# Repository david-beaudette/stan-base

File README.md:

### Install RPi Pico SDK
In a personal folder called projects (could be other):
```bash
cd ~/projects
mkdir pico
cd pico
git clone -b master https://github.com/raspberrypi/pico-sdk.git
cd pico-sdk
git submodule update --init
cd ..
git clone -b master https://github.com/raspberrypi/pico-examples.git
sudo apt update
sudo apt install cmake gcc-arm-none-eabi libnewlib-arm-none-eabi build-essential
cd pico-examples
mkdir build
cd build
echo "export PICO_SDK_PATH=~/projects/pico-sdk" >> ~/.bashrc
source ~/.bashrc
cmake -DCMAKE_BUILD_TYPE=Debug ..
make -j4

```
### Install OpenOCD and debugger
```bash
cd ~/projects/pico
sudo apt install automake autoconf build-essential texinfo libtool libftdi-dev libusb-1.0-0-dev
git clone https://github.com/raspberrypi/openocd.git --recursive --branch rp2040 --depth=1
cd openocd
./bootstrap
./configure --enable-ftdi --enable-sysfsgpio --enable-bcm2835gpio
make -j4
sudo make install
sudo apt install gdb-multiarch

```
### OpenOCD Setup
Add username to the plugdev group to allow non-sudo access to any USB device:
```bash
echo 'SUBSYSTEM=="usb", MODE="0660", GROUP="plugdev"' | sudo tee /etc/udev/rules.d/00-usb-permissions.rules
udevadm control --reload-rules
sudo usermod -a -G plugdev [username]
```
Log out and back in.

### Debugging session
To debug, start opencd in a seperate terminal in the ~/projects/pico/openocd folder:
```bash
cd ~/projects/pico/openocd
src/openocd -f interface/picoprobe.cfg -f target/rp2040.cfg -s tcl
```

### Current state
## Battery voltage reading
Battery / motor ground is decoupled from digital ground. That is good, however the voltage reading is offset and unreliable because of this. Apparently with proper star grounding the grounds could be connected together without issues. Otherwise the most reliable way of achieving this would be to use a seperate DC/DC converter and ADC on the high-power side, and opto-coupler on the digital link to RP2040. 

## Orientation sensor calibration
A proper procedure to calibrate the BNO055 should be written. Ideally it should be automated when/if the robot can achieve it by itself.

## Serial communication with head
The link between base and head (ROS-based) was not completed yet.

## Stability
Finish test_ctl

## LCD
LCD is not working anymore...

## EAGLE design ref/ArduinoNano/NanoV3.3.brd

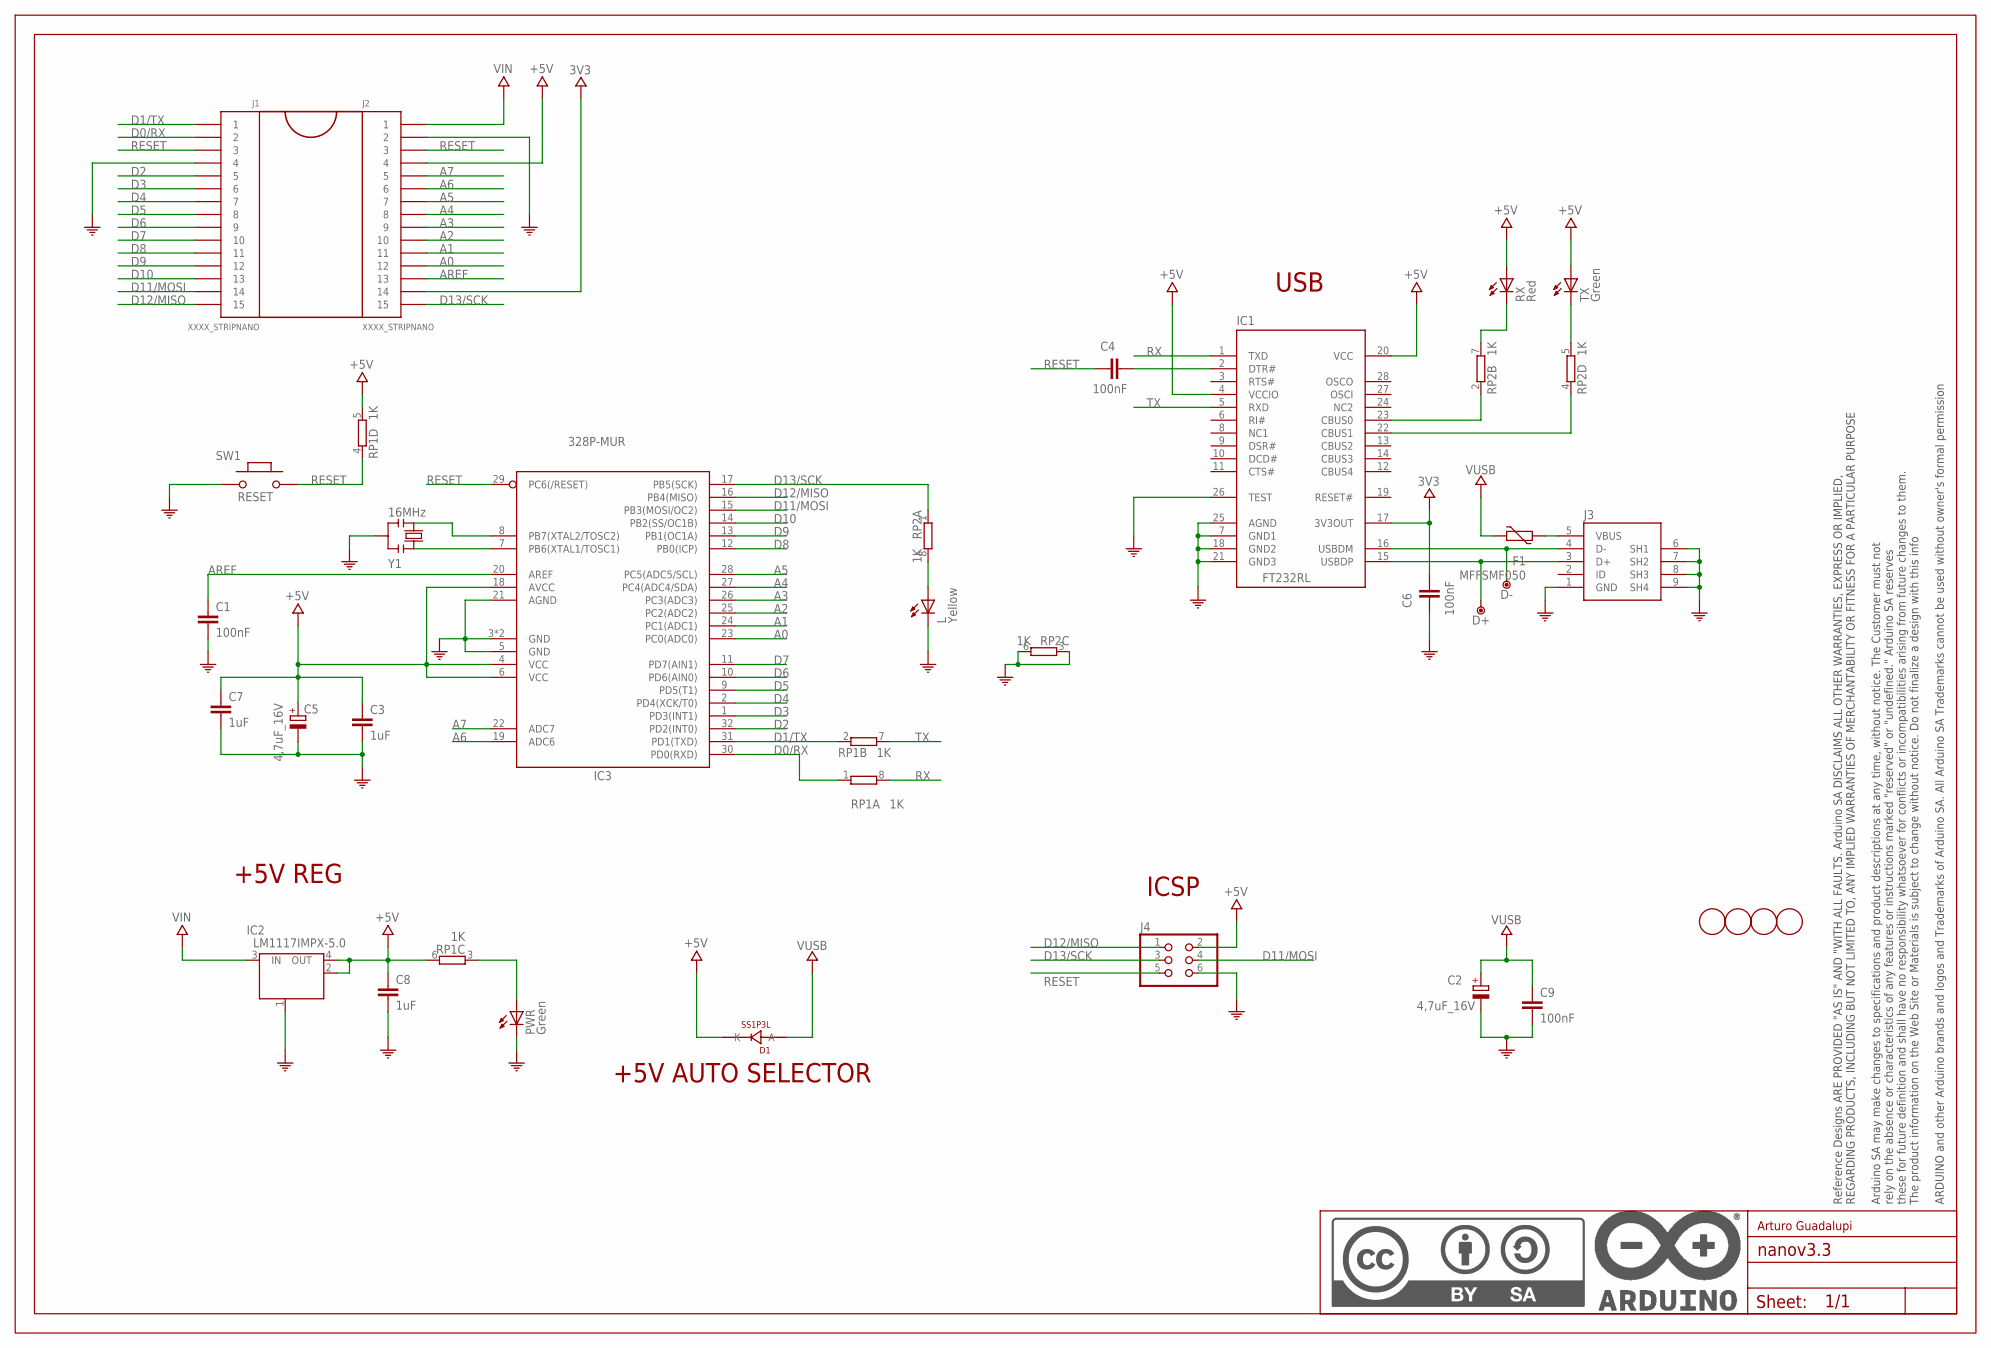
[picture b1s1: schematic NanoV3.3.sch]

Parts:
C1, C4, C6, C9: 100nF; C0603-ROUND
C2, C5: 4,7uF_16V; TAN-A
C3, C7, C8: 1uF; C0603-ROUND
D1: SS1P3L; DO220AAL
D+: DNP; TP-1.00MM
D-: DNP; TP-1.00MM
F1: MFFSMF050; 0603-1608X90N
FRAME1: DNP; FRAME
IC1: FT232RL; SSOP28
IC2: LM1117IMPX-5.0; LINEAR_SOT223
IC3: 328P-MUR; VQFN32
J1, J2: XXXX_STRIPNANO; HEAD15-NOSS
J3: 0219_14850; USB-MINI-B_2
J4: 0114_PH254-203DF118A00V; 2X03
L: Yellow; CHIPLED_0805
PWR: Green; CHIPLED_0805
RP1, RP2: 1K; CAY16
RX: Red; CHIPLED_0805
SW1: RESET; SMD_157SW
TX: Green; CHIPLED_0805
U$4, U$5, U$53, U$54: DNP; FD-1-1.5
Y1: 16MHz; RESONATOR

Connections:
3V3: C6.2, IC1.17 (3V3OUT), J2.14
+5V: C3.1, C5.1 (+), C7.1, C8.1, D1.P$1 (K), IC1.4 (VCCIO), IC1.20 (VCC), IC2.2 (OUT), IC2.4 (OUT), IC3.4 (VCC), IC3.6 (VCC), IC3.18 (AVCC), J2.4, J4.2, RP1.5 (2), RP1.6 (2), RX.A, TX.A
A0: IC3.23 (PC0(ADC0)), J2.12
A1: IC3.24 (PC1(ADC1)), J2.11
A2: IC3.25 (PC2(ADC2)), J2.10
A3: IC3.26 (PC3(ADC3)), J2.9
A4: IC3.27 (PC4(ADC4/SDA)), J2.8
A5: IC3.28 (PC5(ADC5/SCL)), J2.7
A6: IC3.19 (ADC6), J2.6
A7: IC3.22 (ADC7), J2.5
AREF: C1.1, IC3.20 (AREF), J2.13
COM: C1.2, C2.2 (-), C3.2, C5.2 (-), C6.1, C7.2, C8.2, C9.2, IC1.7 (GND1), IC1.18 (GND2), IC1.21 (GND3), IC1.25 (AGND), IC1.26 (TEST), IC2.1 (GND/ADJ), IC3.3 (GND), IC3.5 (GND), IC3.21 (AGND), IC3.33 (GND), J1.4, J2.2, J3.1 (GND), J3.6 (SH1), J3.7 (SH2), J3.8 (SH3), J3.9 (SH4), J4.6, L.C, PWR.C, RP2.3 (1), RP2.6 (2), SW1.1, Y1.2
D0/RX: IC3.30 (PD0(RXD)), J1.2, RP1.1
D1/TX: IC3.31 (PD1(TXD)), J1.1, RP1.2 (1)
D2: IC3.32 (PD2(INT0)), J1.5
D3: IC3.1 (PD3(INT1)), J1.6
D4: IC3.2 (PD4(XCK/T0)), J1.7
D5: IC3.9 (PD5(T1)), J1.8
D6: IC3.10 (PD6(AIN0)), J1.9
D7: IC3.11 (PD7(AIN1)), J1.10
D8: IC3.12 (PB0(ICP)), J1.11
D9: IC3.13 (PB1(OC1A)), J1.12
D10: IC3.14 (PB2(SS/OC1B)), J1.13
D11/MOSI: IC3.15 (PB3(MOSI/OC2)), J1.14, J4.4
D12/MISO: IC3.16 (PB4(MISO)), J1.15, J4.1
D13/SCK: IC3.17 (PB5(SCK)), J2.15, J4.3, RP2.1
unnamed: IC3.8 (PB7(XTAL2/TOSC2)), Y1.3
unnamed: IC3.7 (PB6(XTAL1/TOSC1)), Y1.1
unnamed: PWR.A, RP1.3 (1)
unnamed: C4.2, IC1.2 (DTR#)
unnamed: D+.X, IC1.15 (USBDP), J3.3 (D+)
unnamed: D-.X, IC1.16 (USBDM), J3.4 (D-)
unnamed: L.A, RP2.8 (2)
unnamed: IC1.23 (CBUS0), RP2.2 (1)
unnamed: IC1.22 (CBUS1), RP2.4 (1)
unnamed: RP2.5 (2), TX.C
unnamed: F1.2, J3.5 (VBUS)
unnamed: RP2.7 (2), RX.C
RESET: C4.1, IC3.29 (PC6(/RESET)), J1.3, J2.3, J4.5, RP1.4 (1), SW1.2
RX: IC1.1 (TXD), RP1.8 (2)
TX: IC1.5 (RXD), RP1.7 (2)
VIN: IC2.3 (IN), J2.1
VUSB: C2.1 (+), C9.1, D1.P$2 (A), F1.1

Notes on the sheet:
+5V REG
ICSP
USB
+5V AUTO SELECTOR
Arturo Guadalupi

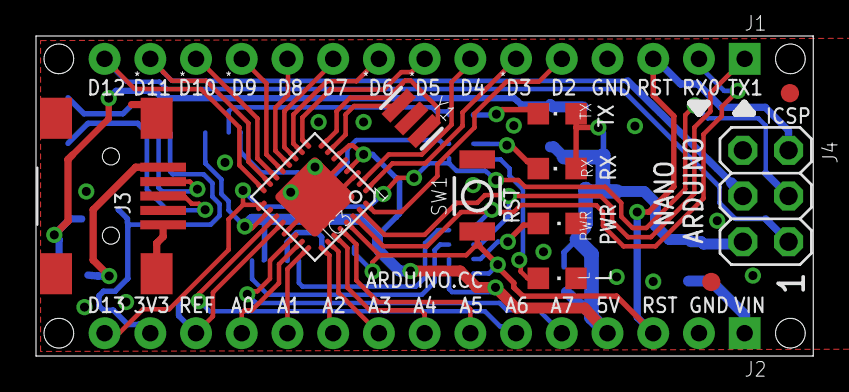
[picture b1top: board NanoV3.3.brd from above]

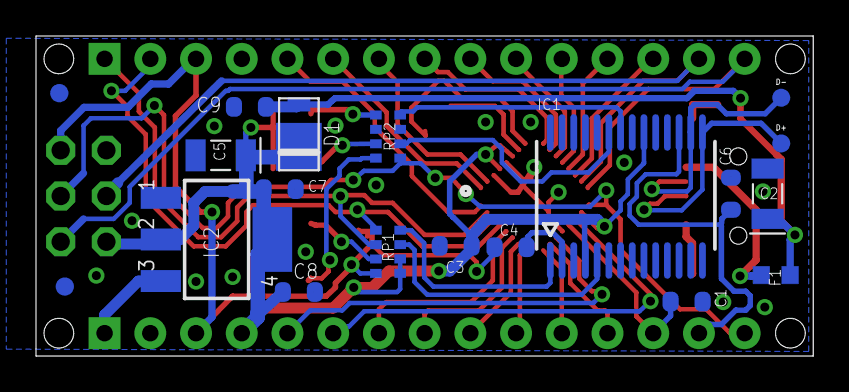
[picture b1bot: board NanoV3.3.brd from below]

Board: 2 copper layers, 43.2 x 17.8 mm, 33 parts (17 on the bottom side), 43 nets.

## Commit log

2021-03-05 Project creation.
2021-03-06 First code with motor driver.
2021-03-07 Interfaced with accelerometer and gyroscope.
2021-03-07 Started listing pins in hal.
2021-03-07 Setup ISR for accelerometer data.
2021-03-08 Added complementary filter and initial sensor bias / offset estimation.
2021-03-08 Starting moving from all in main( ) to periodic tasks.
2021-03-11 Modified code to use scheduled tasks.
2021-03-11 Integrated control function. Morors do not run smooth.
2021-03-12 Motors now orient with pitch. Integrated stepper library.
2021-03-20 Create CTL execute function to run in the main loop
2021-03-21 Added unit test to determine the motor top speed.
2021-03-28 Modified controller to use timer 1 without library.
2021-03-28 Fixed a few bugs. Still holes in the signal.
2021-03-29 Tried more ways to obtain better timing.
2021-03-29 Redesigned pulse generator with tick counter instead of overflow counter.
2021-03-30 Not much progress...
2021-03-31 Set local variables as volatile (not tested yet).
2021-04-01 Succeeded in generating the left motor pulse train.
2021-04-02 Generalised pulse generation for both motors. Still not working.
2021-04-03 Motor control test passed.
2021-04-03 Finalised test to produce expected results.
2021-04-03 Actual commit for last one.
2021-04-03 Modified to perform velocity control using pitch.
2021-04-04 Fixed accelerometer interrupt generation setting. Added state of charge computation to battery monitor function.
2021-04-04 Integrated PID library. Only compensating in one direction...
2021-04-05 Added test for serial communication.
2021-04-17 Linked stan-base with stan-common.
2021-04-18 Implemented serial protocol to send telemetry.
2021-04-18 Removed all serial prints except slow and fast packets.
2021-04-23 Implemented reception of commands.
2021-04-24 Optimised and protected complementary filter.
2021-04-25 Fixed gyro conversion from analog to deg/s.
2021-04-25 Added CRC to protocol. Reset pitch on filter init.
2021-05-01 Now initialisation of filter only averages gyro noise.
2021-05-02 Added tuning actions.
2021-05-08 Added command interface for motor enabling.
2021-05-15 Added tunable filter gain.
2021-05-16 Added system check task.
2021-05-16 Improved gyro bias estimation by using float.
2021-05-22 Prepared for PCB design
2021-05-23 Added more components for PCB design
2021-05-23 Added project specific libraries
2021-05-30 Relocated references and created Fritzing diagram.
2021-05-31 Finished first version of interconnexion diagram.
2021-06-04 Added interconnexion diagram version with connectors and another with protoboard.
2021-07-02 Set Arduino port for Linux
2021-07-02 Merged
2021-07-02 VSCode file was generated.
2021-07-31 Updated protoboard design.
2021-07-31 Started integrating camera module.
2021-07-31 Drafted servo driver based on timer 2 with 2 channels. Test fails.
2021-08-01 Finished implementing camera pan tilt control.
2021-08-01 Integrated cam pan tilt in main program.
2021-08-01 Eliminated some of the jitter when changing servo command.
2021-08-01 Implemented auto camera leveling.
2021-08-08 Setup for remote compilation from RPi.
2021-08-13 Added Python path required after syncing VSCode settings.
2021-10-07 Updated protoboard drawing.
2021-10-23 Added Pico reference
2021-11-06 Transferring code to RPi Pico. Dummy project was setup.
2021-11-07 Integrating rp2040 source in project.
2021-11-07 Added RP2040 reference files and Fritzing designs.
2021-11-07 Added hardware details.
2021-11-07 Created connection diagram for pico.
2021-11-13 Setup test build for camera control.
2021-11-13 Created files for unit test of camera control
2021-11-14 Finished implementing camera servo test.
2021-11-14 Created test and module for potentiometer.
2021-11-15 Used horner function for potentiometer measurement.
2021-11-15 Added potentiometer mapping function.
2021-11-15 Linked pot to camera pan.
2021-11-21 Integrated BNO055 library code and unit test.
2021-11-28 Corrected axis. Added missing state reads.
2021-11-28 Implemented battery voltage / SoC reading. Added motor control.
2021-12-18 Finalised draft of speed to PWM counter conversion function.
2022-01-01 Completed PWM controller. Microstepping control remains.
2022-01-02 Finalised auto control of period for fast / slow speed. Added a second motor test using pot.
2022-01-02 Added pulse counter on PWM.
2022-01-07 Added PID and NAV functions.
2022-01-09 Added reset function. Renamed enum members.
2022-01-09 Added controller function that uses both the motor and pid functions.
2022-01-09 Finished drafting control function.
2022-03-20 Added LCD documentation.
2022-03-20 Created breadboard interconnexion diagram with LCD.
2022-03-20 Added controller unit test (not implemented yet).
2022-03-20 Added unit test for LCD (not implemented yet).
2022-03-20 Merged horner with lib_uti. LCD unit test draft.
2022-03-26 First working version of the LCD interface.
2022-03-26 Fixed renamed include.
2022-03-26 Added direct tuning of Kp. Protection against div/0.
2022-03-26 Started implementing CTL test.
2022-06-18 Prepared control test. Added sharing of launch and Cpp properties file.
2023-07-08 Improved debug setup description.
2023-07-08 Improved debug section description.
2023-07-08 Added launch config that does not stop at main.
2023-07-08 Added robot status section.

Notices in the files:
parts and their libraries:
Arduino-utility: Copyright (c) 2016-2017 Arduino LLC.  All right reserved.
